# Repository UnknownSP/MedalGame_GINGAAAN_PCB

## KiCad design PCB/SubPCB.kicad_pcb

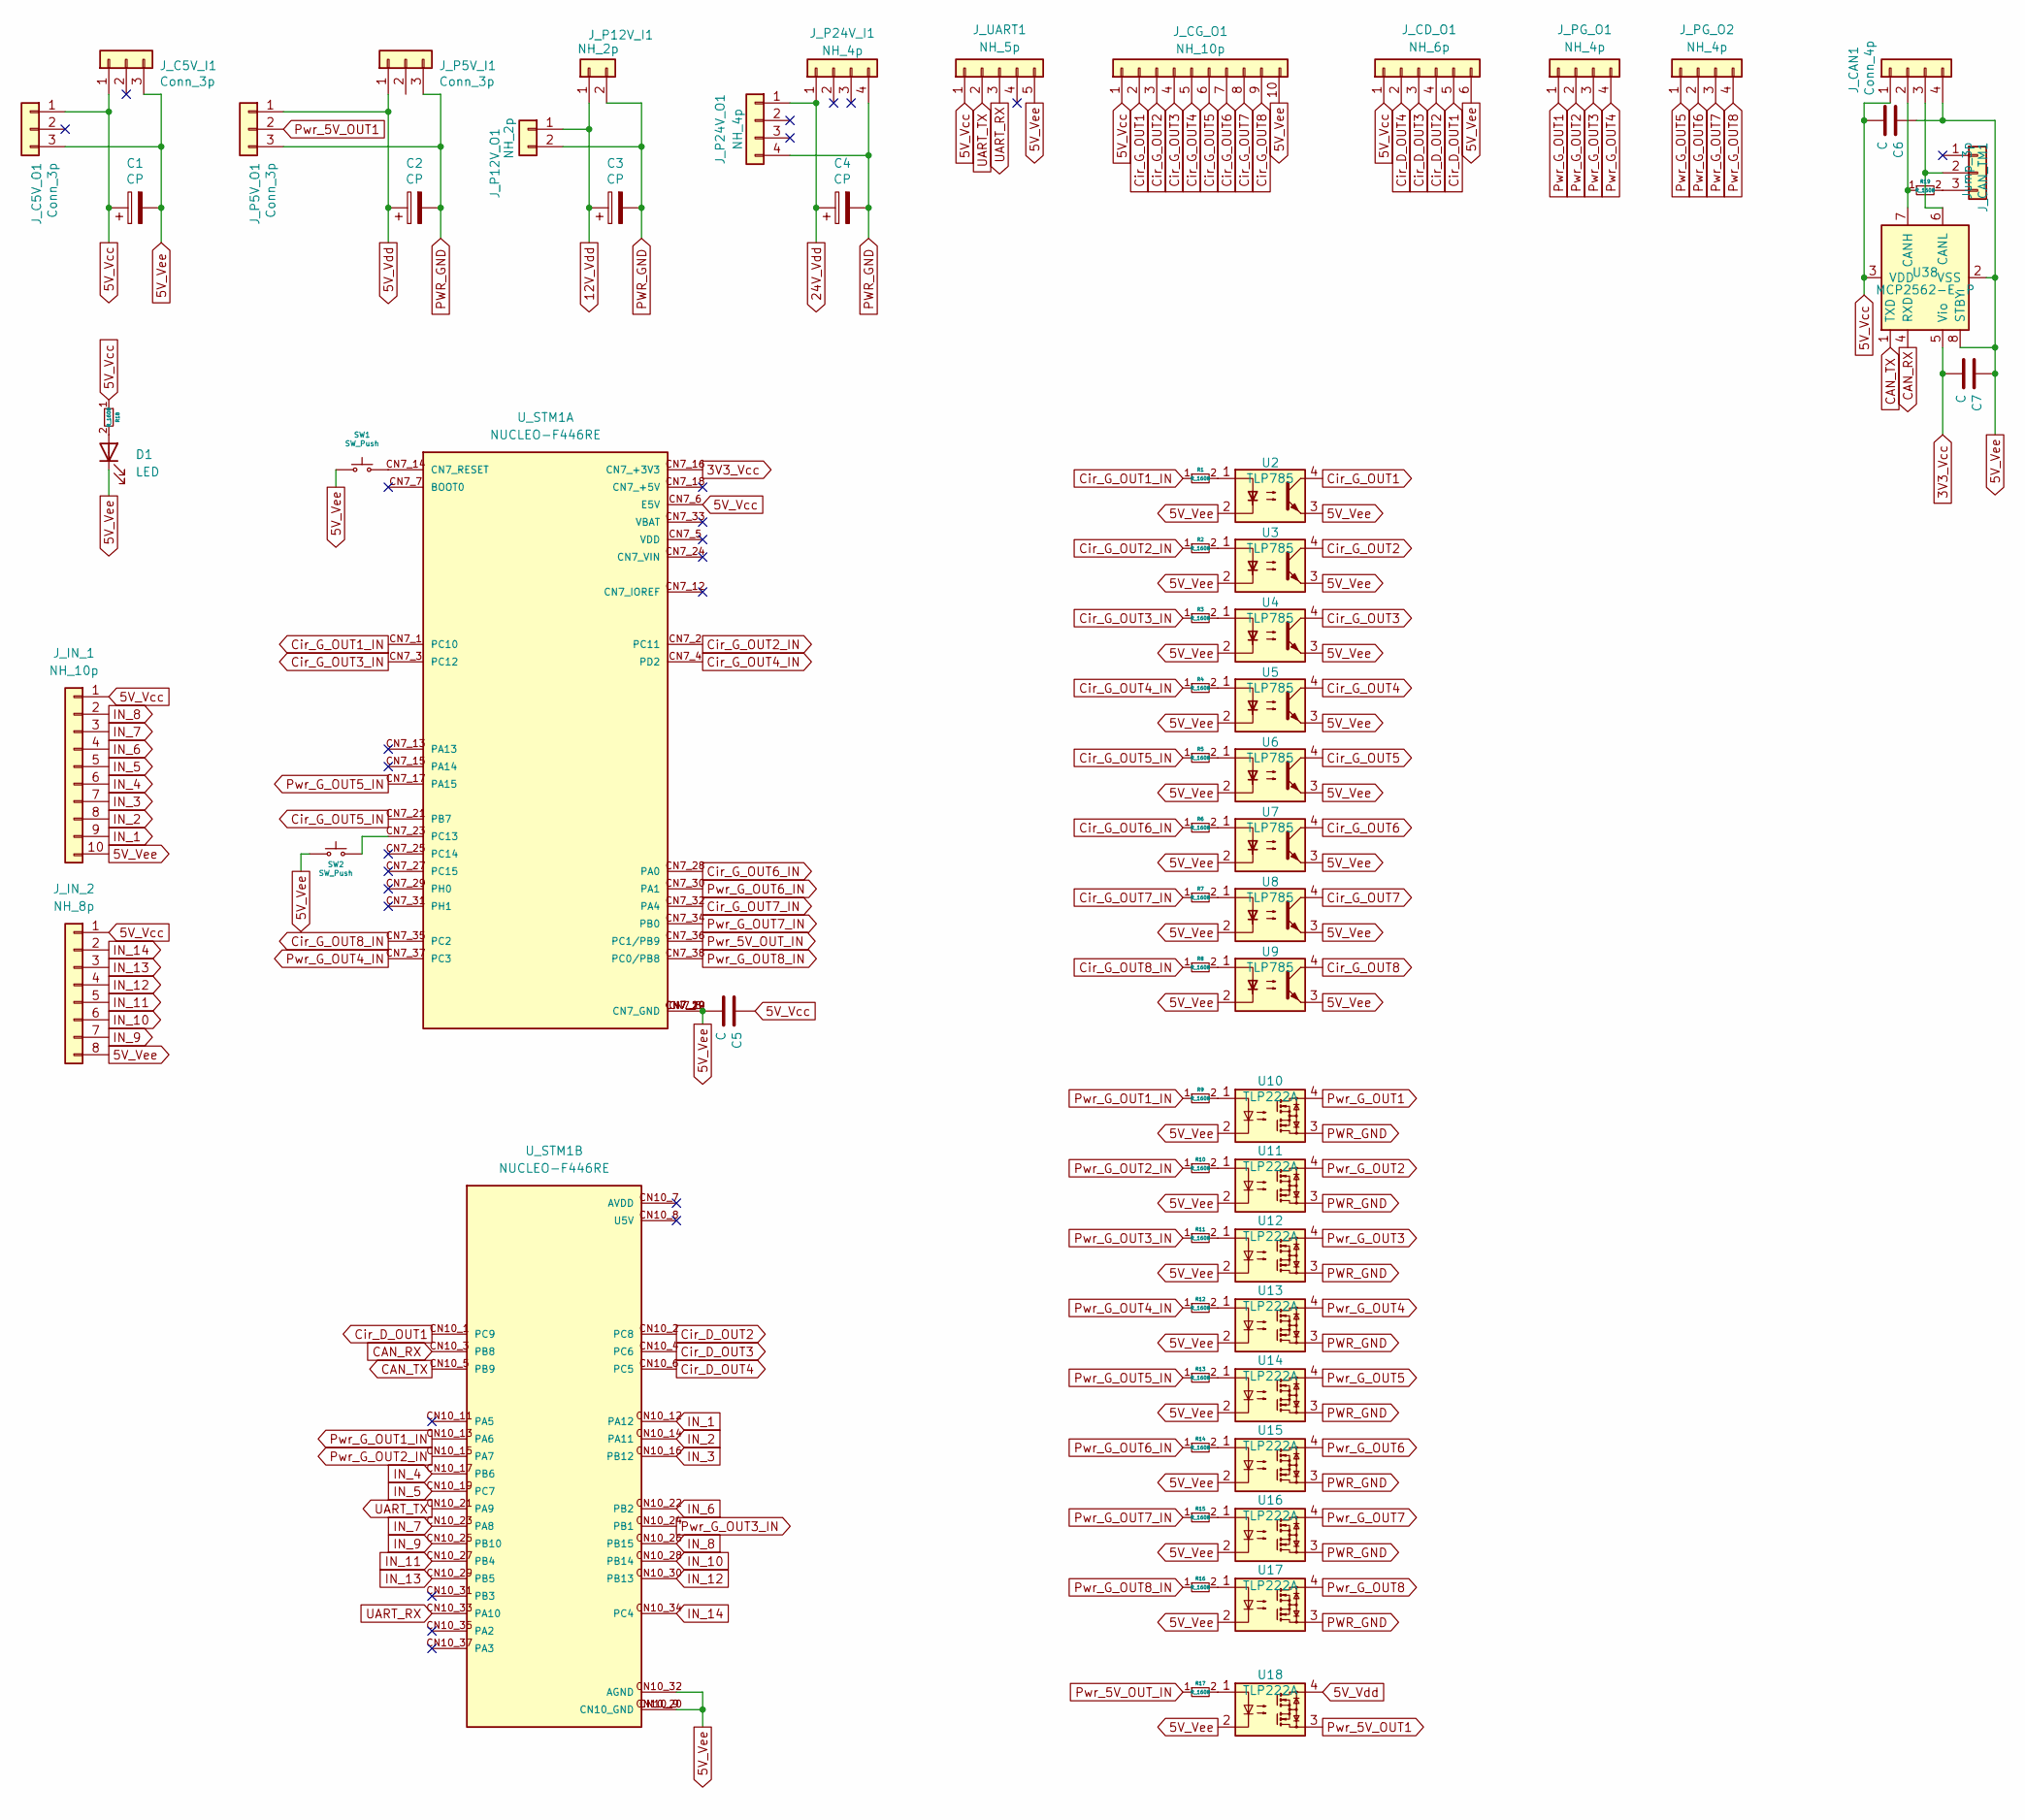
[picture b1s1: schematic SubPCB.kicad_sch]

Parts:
C1, C2, C3, C4: CP; C
C5, C6, C7: C
D1: LED; LED_0603_1608Metric_Pad1.05x0.95mm_HandSolder
J_C5V_I1, J_C5V_O1: Conn_3p; Conn_3pin
J_CAN1: Conn_4p; Conn_4pin
J_CAN_TM1: Jump_3p; Conn_3pin
J_CD_O1: NH_6p; Conn_6pin
J_CG_O1: NH_10p; Conn_10pin
J_IN_1: NH_10p; Conn_10pin
J_IN_2: NH_8p; Conn_8pin
J_P5V_I1, J_P5V_O1: Conn_3p; Conn_3pin
J_P12V_I1, J_P12V_O1: NH_2p; Conn_2pin
J_P24V_I1, J_P24V_O1: NH_4p; Conn_4pin
J_PG_O1, J_PG_O2: NH_4p; Conn_4pin
J_UART1: NH_5p; Conn_5pin
R1, R2, R3, R4, R5, R6, R7, R8, R9, R10, R11, R12, R13, R14, R15, R16, R17, R18, R19: R_1608; R_0603_1608Metric_Pad0.98x0.95mm_HandSolder
SW1, SW2: SW_Push; SW_PUSH_6mm_H5mm
U2, U3, U4, U5, U6, U7, U8, U9: TLP785; DIP-4_W7.62mm
U10, U11, U12, U13, U14, U15, U16, U17, U18: TLP222A; DIP-4_W7.62mm
U38: MCP2562-E-P; DIP-8_W7.62mm
U_STM1: NUCLEO-F446RE; MODULE_NUCLEO-F446RE; PARTREV 13

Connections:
3V3_Vcc: C7.2, U38.5 (Vio), U_STM1.CN7_16 (CN7_+3V3)
5V_Vcc: C1.1, C5.1, C6.2, J_C5V_I1.1, J_C5V_O1.1, J_CAN1.1, J_CD_O1.1, J_CG_O1.1, J_IN_1.1, J_IN_2.1, J_UART1.1, R18.1, U38.3 (VDD), U_STM1.CN7_6 (E5V)
5V_Vdd: C2.1, J_P5V_I1.1, J_P5V_O1.1, U18.4
5V_Vee: C1.2, C5.2, C6.1, C7.1, D1.1 (K), J_C5V_I1.3, J_C5V_O1.3, J_CAN1.4, J_CD_O1.6, J_CG_O1.10 (Pin_9), J_IN_1.10 (Pin_9), J_IN_2.8, J_UART1.5, SW1.1, SW2.1, U2.2, U2.3, U3.2, U3.3, U4.2, U4.3, U5.2, U5.3, U6.2, U6.3, U7.2, U7.3, U8.2, U8.3, U9.2, U9.3, U10.2, U11.2, U12.2, U13.2, U14.2, U15.2, U16.2, U17.2, U18.2, U38.2 (VSS), U38.8 (STBY), U_STM1.CN7_8 (CN7_GND), U_STM1.CN7_19 (CN7_GND), U_STM1.CN7_20 (CN7_GND), U_STM1.CN7_22 (CN7_GND), U_STM1.CN10_9 (CN10_GND), U_STM1.CN10_20 (CN10_GND), U_STM1.CN10_32 (AGND); also elsewhere on the board
12V_Vdd: C3.1, J_P12V_I1.1, J_P12V_O1.1
24V_Vdd: C4.1, J_P24V_I1.1, J_P24V_O1.1
CAN_RX: U38.4 (RXD), U_STM1.CN10_3 (PB8)
CAN_TX: U38.1 (TXD), U_STM1.CN10_5 (PB9)
Cir_D_OUT1: J_CD_O1.5, U_STM1.CN10_1 (PC9)
Cir_D_OUT2: J_CD_O1.4, U_STM1.CN10_2 (PC8)
Cir_D_OUT3: J_CD_O1.3, U_STM1.CN10_4 (PC6)
Cir_D_OUT4: J_CD_O1.2, U_STM1.CN10_6 (PC5)
Cir_G_OUT1: J_CG_O1.2, U2.4
Cir_G_OUT1_IN: R1.1, U_STM1.CN7_1 (PC10)
Cir_G_OUT2: J_CG_O1.3, U3.4
Cir_G_OUT2_IN: R2.1, U_STM1.CN7_2 (PC11)
Cir_G_OUT3: J_CG_O1.4, U4.4
Cir_G_OUT3_IN: R3.1, U_STM1.CN7_3 (PC12)
Cir_G_OUT4: J_CG_O1.5, U5.4
Cir_G_OUT4_IN: R4.1, U_STM1.CN7_4 (PD2)
Cir_G_OUT5: J_CG_O1.6, U6.4
Cir_G_OUT5_IN: R5.1, U_STM1.CN7_21 (PB7)
Cir_G_OUT6: J_CG_O1.7, U7.4
Cir_G_OUT6_IN: R6.1, U_STM1.CN7_28 (PA0)
Cir_G_OUT7: J_CG_O1.8, U8.4
Cir_G_OUT7_IN: R7.1, U_STM1.CN7_32 (PA4)
Cir_G_OUT8: J_CG_O1.9, U9.4
Cir_G_OUT8_IN: R8.1, U_STM1.CN7_35 (PC2)
IN_1: J_IN_1.9, U_STM1.CN10_12 (PA12)
IN_2: J_IN_1.8, U_STM1.CN10_14 (PA11)
IN_3: J_IN_1.7, U_STM1.CN10_16 (PB12)
IN_4: J_IN_1.6, U_STM1.CN10_17 (PB6)
IN_5: J_IN_1.5, U_STM1.CN10_19 (PC7)
IN_6: J_IN_1.4, U_STM1.CN10_22 (PB2)
IN_7: J_IN_1.3, U_STM1.CN10_23 (PA8)
IN_8: J_IN_1.2, U_STM1.CN10_26 (PB15)
IN_9: J_IN_2.7, U_STM1.CN10_25 (PB10)
IN_10: J_IN_2.6, U_STM1.CN10_28 (PB14)
IN_11: J_IN_2.5, U_STM1.CN10_27 (PB4)
IN_12: J_IN_2.4, U_STM1.CN10_30 (PB13)
IN_13: J_IN_2.3, U_STM1.CN10_29 (PB5)
IN_14: J_IN_2.2, U_STM1.CN10_34 (PC4)
unnamed 42: D1.2 (A), R18.2; also elsewhere on the board
unnamed: J_CAN1.2, R19.1, U38.7 (CANH)
unnamed: J_CAN1.3, J_CAN_TM1.2, U38.6 (CANL)
unnamed: J_CAN_TM1.3, R19.2
unnamed: R1.2, U2.1
unnamed: R2.2, U3.1
unnamed: R3.2, U4.1
unnamed: R4.2, U5.1
unnamed: R5.2, U6.1
unnamed: R6.2, U7.1
unnamed: R7.2, U8.1
unnamed: R8.2, U9.1
unnamed: R9.2, U10.1
unnamed: R10.2, U11.1
unnamed: R11.2, U12.1
unnamed: R12.2, U13.1
unnamed: R13.2, U14.1
unnamed: R14.2, U15.1
unnamed: R15.2, U16.1
unnamed: R16.2, U17.1
unnamed: R17.2, U18.1
unnamed 63: SW1.2, U_STM1.CN7_14 (CN7_RESET); also elsewhere on the board
unnamed 64: SW2.2, U_STM1.CN7_23 (PC13); also elsewhere on the board
PWR_GND: C2.2, C3.2, C4.2, J_P5V_I1.3, J_P5V_O1.3, J_P12V_I1.2, J_P12V_O1.2, J_P24V_I1.4, J_P24V_O1.4, U10.3, U11.3, U12.3, U13.3, U14.3, U15.3, U16.3, U17.3
Pwr_5V_OUT1: J_P5V_O1.2, U18.3
Pwr_5V_OUT_IN: R17.1, U_STM1.CN7_36 (PC1/PB9)
Pwr_G_OUT1: J_PG_O1.1, U10.4
Pwr_G_OUT1_IN: R9.1, U_STM1.CN10_13 (PA6)
Pwr_G_OUT2: J_PG_O1.2, U11.4
Pwr_G_OUT2_IN: R10.1, U_STM1.CN10_15 (PA7)
Pwr_G_OUT3: J_PG_O1.3, U12.4
Pwr_G_OUT3_IN: R11.1, U_STM1.CN10_24 (PB1)
Pwr_G_OUT4: J_PG_O1.4, U13.4
Pwr_G_OUT4_IN: R12.1, U_STM1.CN7_37 (PC3)
Pwr_G_OUT5: J_PG_O2.1, U14.4
Pwr_G_OUT5_IN: R13.1, U_STM1.CN7_17 (PA15)
Pwr_G_OUT6: J_PG_O2.2, U15.4
Pwr_G_OUT6_IN: R14.1, U_STM1.CN7_30 (PA1)
Pwr_G_OUT7: J_PG_O2.3, U16.4
Pwr_G_OUT7_IN: R15.1, U_STM1.CN7_34 (PB0)
Pwr_G_OUT8: J_PG_O2.4, U17.4
Pwr_G_OUT8_IN: R16.1, U_STM1.CN7_38 (PC0/PB8)
UART_RX: J_UART1.3, U_STM1.CN10_33 (PA10)
UART_TX: J_UART1.2, U_STM1.CN10_21 (PA9)

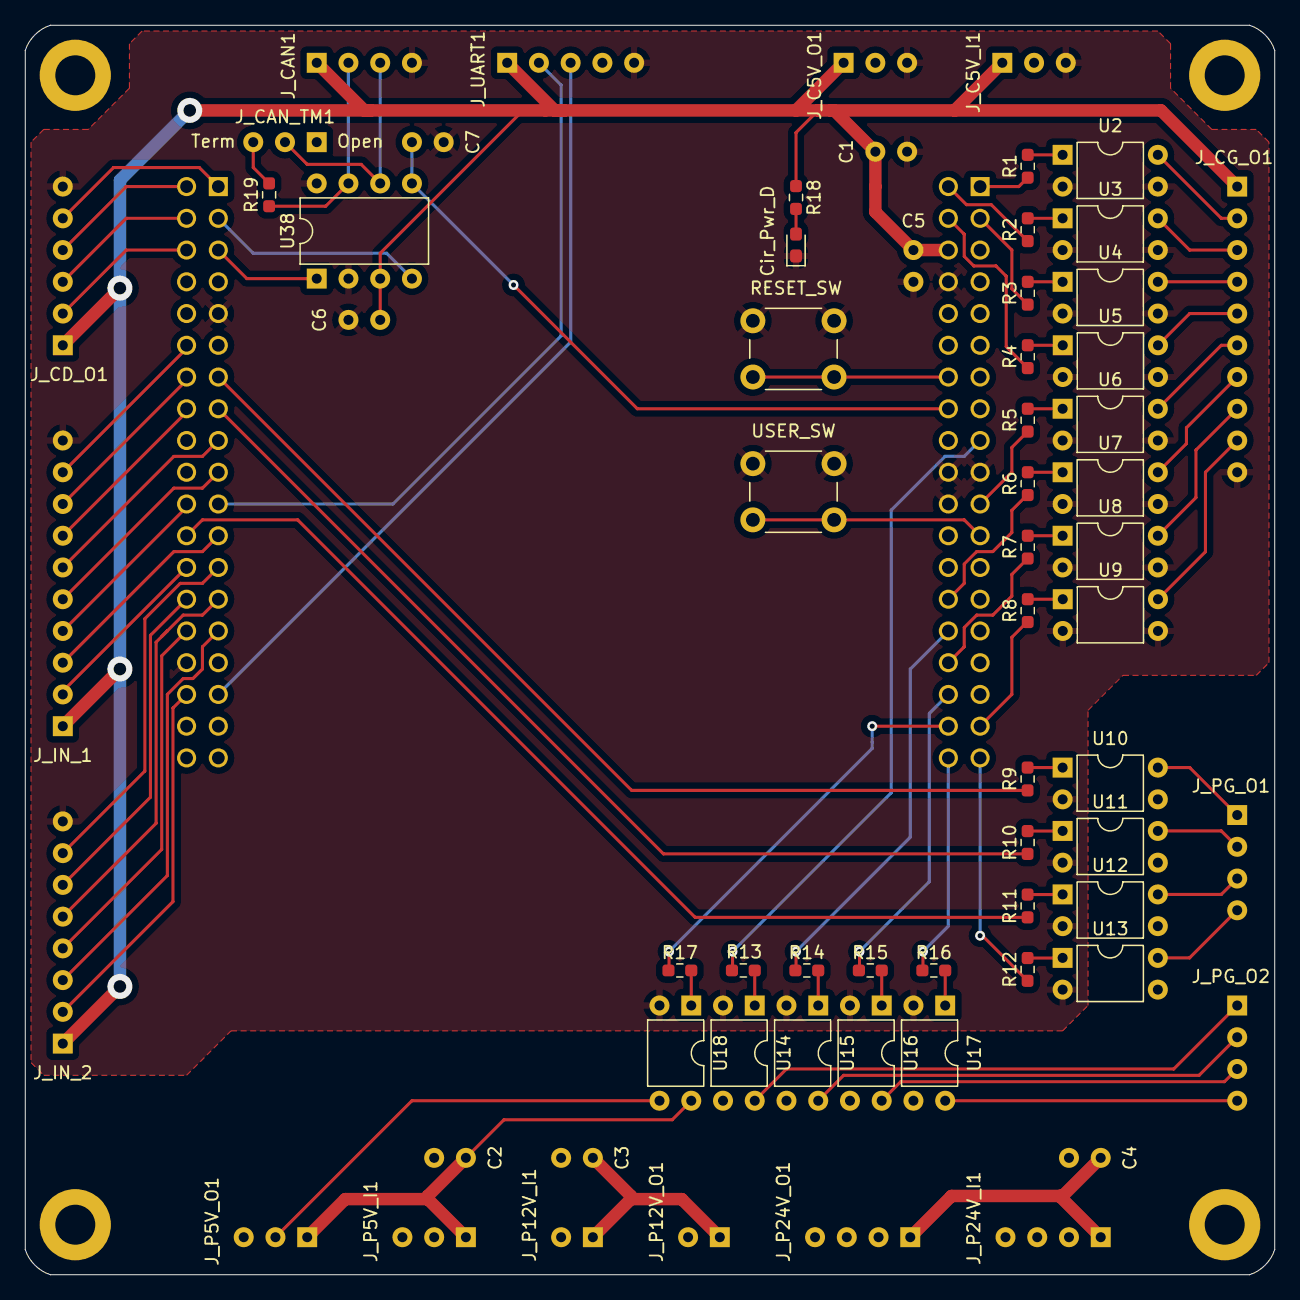
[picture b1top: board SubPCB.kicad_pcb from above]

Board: 2 copper layers, 100.0 x 100.0 mm, 69 parts (1 on the bottom side), 86 nets.

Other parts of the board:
Cir_Pwr_D: LED; LED_0603_1608Metric_Pad1.05x0.95mm_HandSolder
REF1, REF1#2, REF1#3, REF1#4: MountingHole_3.2mm_M3_ISO7380_Pad
RESET_SW: SW_Push; SW_PUSH_6mm_H5mm
USER_SW: SW_Push; SW_PUSH_6mm_H5mm

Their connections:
5V_Vee: Cir_Pwr_D.1 (K), RESET_SW.1, USER_SW.1; also elsewhere on the board
unnamed 42: Cir_Pwr_D.2 (A); also elsewhere on the board
unnamed 63: RESET_SW.2; also elsewhere on the board
unnamed 64: USER_SW.2; also elsewhere on the board
